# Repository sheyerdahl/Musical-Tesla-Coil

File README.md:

Welcome
======
A DRSSTC (Dual Resonant Solid State Tesla Coil) project that uses the ESP32-S3-WROOM-1 module as the microcontroller and wireless communication. 

My primary circuit uses the SKM100GB125DN IGBT

Notes
-------
The first revision (REV 1.0) being my first PCB, had quite a few issues and oversights. REV 2.0 will fix these issues, although it will be untested.
Some of the issues that were fixed:

Lack of OCD Comparator
Lack of peak detector circuit for measuring current
Lack of ZCD Comparator
USB-C footprint being incorrect
Slow diodes being used in the GDT circuit
Lack of mounting holes
Using built-in ADC of ESP32, an external one would have significantly more ENOB. (Effective Number Of Bits)
No Reverse polarity protection, no over current protection.

Credits
-------
Most design decisions were made because of Mads Barnkob and his awesome [website](https://kaizerpowerelectronics.dk/tesla-coils/drsstc-design-guide/) and [Youtube videos](https://www.youtube.com/@KaizerPowerElectronicsDk).

Thanks to those who worked on the [UD3 Board](https://github.com/Netzpfuscher/UD3), some of their hardware design was copied to this one.

[JAVATC3D](https://www.classictesla.com/java/javatc3d/javatc3d.html)

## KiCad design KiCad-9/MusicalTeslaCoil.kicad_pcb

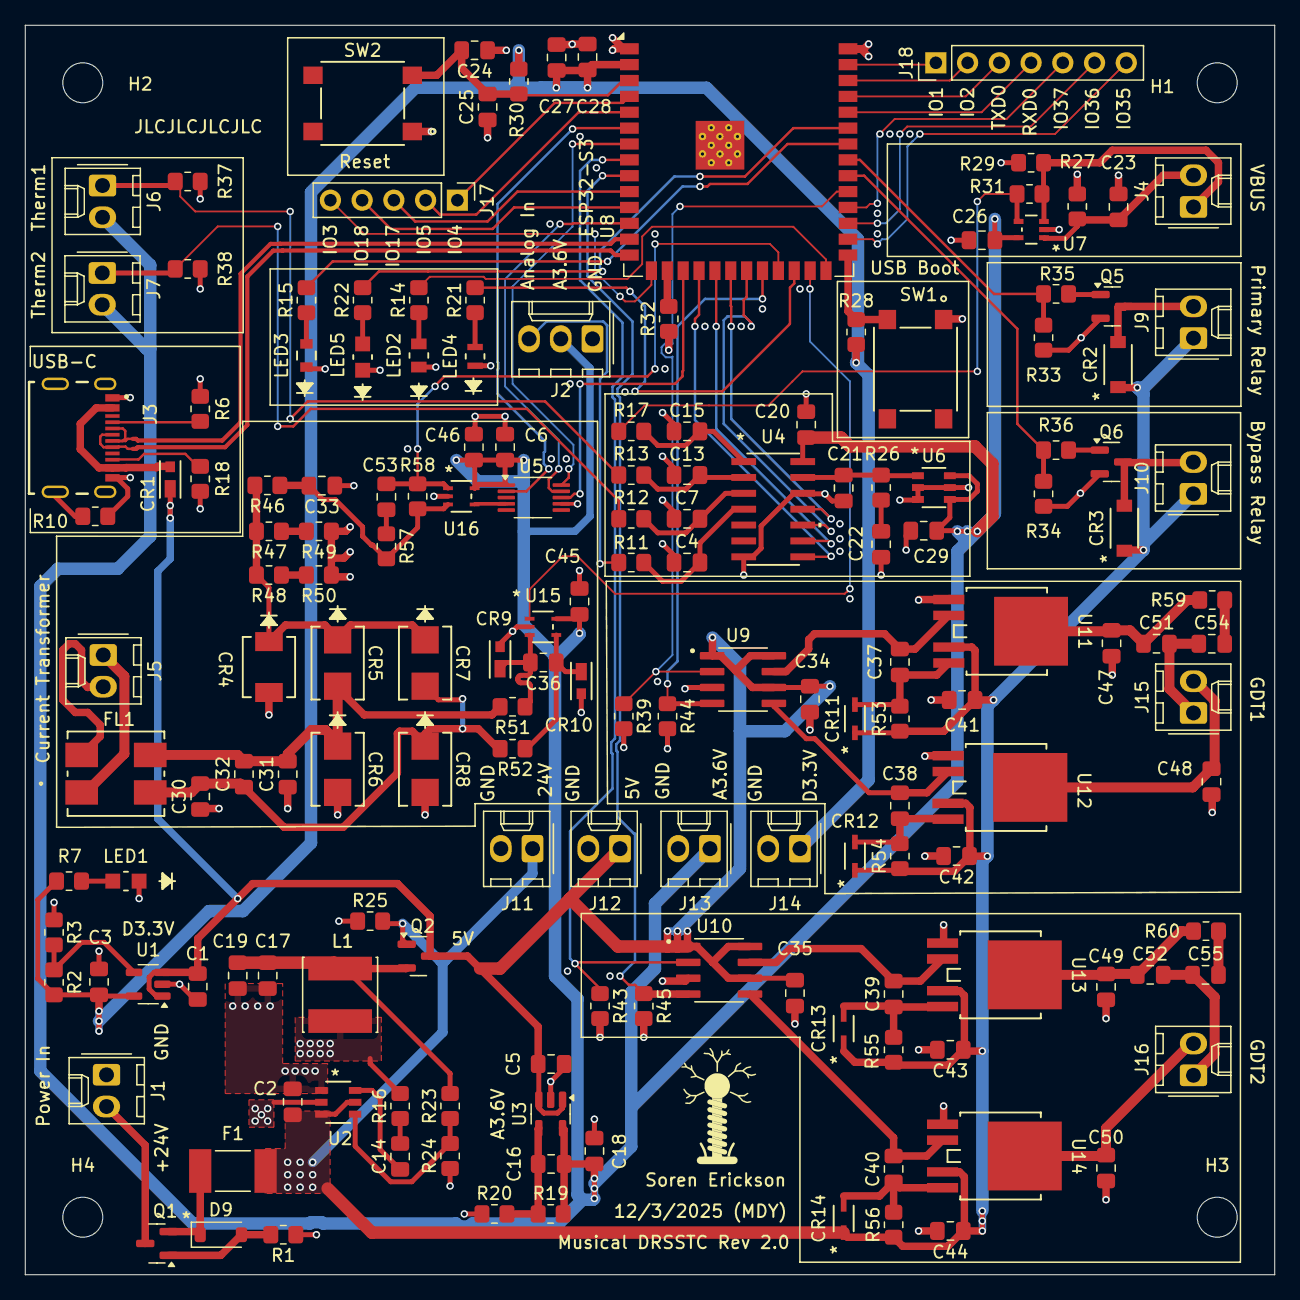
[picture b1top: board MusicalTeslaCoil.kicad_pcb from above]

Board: 4 copper layers, 100.0 x 100.0 mm, 169 parts (0 on the bottom side), 105 nets.

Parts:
C1, C3, C5, C18, C20, C22, C29, C51, C52: 2.2uF; C_0805_2012Metric_Pad1.18x1.45mm_HandSolder
C2, C17, C19, C27, C28: 10uF; C_0805_2012Metric_Pad1.18x1.45mm_HandSolder
C4, C7, C13, C15, C16, C23: 10nF; C_0805_2012Metric_Pad1.18x1.45mm_HandSolder
C6, C25, C45, C46, C54, C55: 1uF; C_0805_2012Metric_Pad1.18x1.45mm_HandSolder
C14, C24, C26, C37, C38, C39, C40: 0.1uF; C_0805_2012Metric_Pad1.18x1.45mm_HandSolder
C21, C32, C47, C48, C49, C50: 1nF; C_0805_2012Metric_Pad1.18x1.45mm_HandSolder
C30, C31, C33, C36: 150pF; C_0805_2012Metric_Pad1.18x1.45mm_HandSolder
C34, C35, C41, C42, C43, C44: 4.7uF; C_0805_2012Metric_Pad1.18x1.45mm_HandSolder
C53: 470pF; C_0805_2012Metric_Pad1.18x1.45mm_HandSolder
CR1, CR9, CR10: MSS1P4-M3/89A; DIODE_MSP3V3
CR2, CR3: 1N4007FL; CR_SOD-123FL_SME
CR4: SMBJ3V3-E3/52; CR_V3-E3&slash_52_VIS
CR5, CR6, CR7, CR8: ES2B-E3/52T; DO-214AA_VIS
CR11, CR12, CR13, CR14: 1N4148WS-7-F; CR_SOD323_MCC
D9: BZT52C15-7-F; D_SOD-123
F1: 0ZCG0050AF2C; FUSER_0ZCG0050AF2C
FL1: WCM 7060FASF-701-LM; FL4_WCM7060_TTA
H1, H2, H3, H4: MountingHole; MountingHole_3.2mm_M3
J1: Power in; Molex_KK-254_AE-6410-02A_1x02_P2.54mm_Vertical
J2: Conn_01x03; Molex_KK-254_AE-6410-03A_1x03_P2.54mm_Vertical
J3: USB4215-03-A; USB4215_03_A
J4: VBUS; Molex_KK-254_AE-6410-02A_1x02_P2.54mm_Vertical
J5: Current Transformer; Molex_KK-254_AE-6410-02A_1x02_P2.54mm_Vertical
J6: NTC Thermistor 1; Molex_KK-254_AE-6410-02A_1x02_P2.54mm_Vertical
J7: NTC Thermistor 2; Molex_KK-254_AE-6410-02A_1x02_P2.54mm_Vertical
J9: Primary Relay; Molex_KK-254_AE-6410-02A_1x02_P2.54mm_Vertical
J10: Soft Start Bypass Relay; Molex_KK-254_AE-6410-02A_1x02_P2.54mm_Vertical
J11, J12, J13, J14: Conn_01x02; Molex_KK-254_AE-6410-02A_1x02_P2.54mm_Vertical
J15: GDT1; Molex_KK-254_AE-6410-02A_1x02_P2.54mm_Vertical
J16: GDT2; Molex_KK-254_AE-6410-02A_1x02_P2.54mm_Vertical
J17: Conn_01x05; PinHeader_1x05_P2.54mm_Vertical
J18: Conn_01x07; PinHeader_1x07_P2.54mm_Vertical
L1: VLS6045EX-150M; VLS6045EX_150M
LED1, LED5: LTST-C170GKT; LED_LTST-C170GKT_LTO
LED2: LTST-C170KFKT; LED_LTST-C170KFKT_LTO
LED3: LTST-C171KRKT; LED_LTST-C171_LTO
LED4: LTST-C170KSKT; LED_LTST-C170KSKT_LTO
Q1: GSF3407; SOT-23
Q2: SSF7912; SOT-23
Q5, Q6: 2N7002K; SOT-23
R1, R6, R18: 5.1k; R_0805_2012Metric_Pad1.20x1.40mm_HandSolder
R2, R19, R24, R29, R31: 3k; R_0805_2012Metric_Pad1.20x1.40mm_HandSolder
R3: 15k; R_0805_2012Metric_Pad1.20x1.40mm_HandSolder
R7, R14, R15, R21, R22, R57: 150; R_0805_2012Metric_Pad1.20x1.40mm_HandSolder
R10: 100k; R_0805_2012Metric_Pad1.20x1.40mm_HandSolder
R11, R12, R13, R17, R37, R38, R46, R51, R52, R53, R54, R55, R56: 1k; R_0805_2012Metric_Pad1.20x1.40mm_HandSolder
R16: 0; R_0805_2012Metric_Pad1.20x1.40mm_HandSolder
R20: 16.5k; R_0805_2012Metric_Pad1.20x1.40mm_HandSolder
R23: 22k; R_0805_2012Metric_Pad1.20x1.40mm_HandSolder
R25, R28, R30, R32, R33, R34, R39, R43, R44, R45: 10k; R_0805_2012Metric_Pad1.20x1.40mm_HandSolder
R26, R35, R36: 51; R_0805_2012Metric_Pad1.20x1.40mm_HandSolder
R27: 1.5k; R_0805_2012Metric_Pad1.20x1.40mm_HandSolder
R47, R48, R49, R50: 3.3 0.5W; R_0805_2012Metric_Pad1.20x1.40mm_HandSolder
R58: 200k; R_0805_2012Metric_Pad1.20x1.40mm_HandSolder
R59, R60: 15; R_0805_2012Metric_Pad1.20x1.40mm_HandSolder
SW1: USB Boot; SO4_222A-M-V-B_CTS
SW2: Reset; SO4_222A-M-V-B_CTS
U1, U3: TLV75801PDBV; SOT-23-5
U2: TPP362082-T6TR; TSOT23-6-A_TPK
U4: MCP3204T-CI/SL; SOIC14-N_MC_MCH
U5: MCP48FVB11
U6: MCP1501T-33E/CHY; SOT-23-6_CHY_MCH
U7: MCP6006UT-E/LT; SC70-5_LT_MCH
U8: ESP32-S3-WROOM-1
U9, U10: UCC27423DR; SOIC127P599X175-8N
U11, U12, U13, U14: DMC4029SK4-13; TO252-4_DMC4029SK4-13_DIO
U15, U16: NCS2250SQ2T2G; SC70-5_2P2X1P35_ONS

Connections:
5V: C1.2, C5.2, C34.2, C35.2, CR1.1, J12.1, Q2.3 (D), U1.1 (IN), U1.3 (EN), U3.1 (IN), U3.3 (EN), U9.1 (ENBA), U9.6 (VDD), U9.8 (ENBB), U10.1 (ENBA), U10.6 (VDD), U10.8 (ENBB)
24V: C2.1, C41.1, C42.1, C43.1, C44.1, CR2.1, CR3.1, CR11.1, CR12.1, CR13.1, CR14.1, F1.1, J9.1, J10.1, J11.1, Q2.1 (G), R25.2, R53.1, R54.1, R55.1, R56.1, U2.3 (VIN), U2.5 (EN), U11.3 (P-Chan_S), U12.3 (P-Chan_S), U13.3 (P-Chan_S), U14.3 (P-Chan_S)
A3.6V: C6.2, C16.2, C18.2, C20.2, C26.2, C29.2, C45.2, C46.2, J2.2, J6.2, J7.2, J13.1, R19.2, U3.5 (OUT), U4.14 (VDD), U5.1 (VDD), U6.4 (*SHDN), U6.6 (VDD), U7.5 (V+), U15.5 (V+), U16.5 (V+)
ADC_CLK: U4.11 (CLK), U8.20 (IO12)
ADC_CS: U4.8 (*CS/SHDN), U8.18 (IO10)
ADC_DIN: U4.9 (DIN), U8.19 (IO11)
ADC_DOUT: U4.10 (DOUT), U8.21 (IO13)
BypassRelay: R34.1, R36.2, U8.32 (IO39)
CTOut: C33.2, R46.1, R57.2, R58.2, U16.3 (+)
D3.3V: C3.2, C27.2, C28.1, J14.1, R2.2, R7.2, R28.1, R30.1, U1.5 (OUT), U8.2 (3V3)
DACVOut: U5.4 (VOut), U16.4 (-)
DAC_CLK: U5.9 (SCK), U8.12 (IO8)
DAC_CS: U5.2 (*CS), U8.6 (IO6)
DAC_DIN: U5.10 (SDI), U8.7 (IO7)
DAC_DOUT: U5.8 (SDO), U8.17 (IO9)
GD1-A: R39.1, U8.31 (IO38), U9.2 (INA)
GD1-B: R44.1, U8.22 (IO14), U9.4 (INB)
GD2-A: R43.1, U8.8 (IO15), U10.2 (INA)
GD2-B: R45.1, U8.9 (IO16), U10.4 (INB)
GND: C1.1, C2.2, C3.1, C4.1, C5.1, C6.1, C7.1, C13.1, C15.1, C17.2, C18.1, C19.2, C20.1, C21.1, C22.1, C23.1, C24.1, C25.1, C26.1, C27.1, C28.2, C29.1, C30.1, C31.1, C33.1, C34.1, C35.1, C41.2, C42.2, C43.2, C44.2, C45.1, C46.1, C47.2, C48.2, C49.2, C50.2, CR4.2, CR6.2, CR8.2, CR9.2, CR10.2, J1.1, J2.1, J3.A1_B12 (GND_A), J3.B1_A12 (GND_B), J11.2, J12.2, J13.2, J14.2, LED1.1, LED2.1, LED3.1, LED4.1, LED5.1, Q5.2 (S), Q6.2 (S), R1.1, R3.1, R6.1, R10.2, R18.1, R20.1, R24.1, R25.1, R27.1, R29.1, R32.1, R33.2, R34.2, R37.2, R38.2, R39.2, R43.2, R44.2, R45.2, R49.1, R50.1, SW1.1 (A), SW2.1 (A), U1.2 (GND), U2.1 (GND), U3.2 (GND), U4.7 (DGND), U4.12 (AGND), U5.7 (GND), U6.2 (GND), U6.3 (GND), U6.5 (GND), U7.2 (V-), U8.1 (GND), U8.40 (GND), U8.41 (GND), U9.3 (GND), U10.3 (GND), U11.1 (N-Chan_S), U12.1 (N-Chan_S), U13.1 (N-Chan_S), U14.1 (N-Chan_S), U15.2 (V-), U16.2 (V-)
IO1: J18.1, U8.39 (IO1)
IO2: J18.2, U8.38 (IO2)
IO3: J17.5, U8.15 (IO3)
IO4: J17.1, U8.4 (IO4)
IO5: J17.2, U8.5 (IO5)
IO17: J17.3, U8.10 (IO17)
IO18: J17.4, U8.11 (IO18)
IO35: J18.7, U8.28 (IO35)
IO36: J18.6, U8.29 (IO36)
IO37: J18.5, U8.30 (IO37)
LED1: R15.2, U8.34 (IO41)
LED2: R22.2, U8.35 (IO42)
LED3: R14.2, U8.26 (IO45)
LED4: R21.2, U8.24 (IO47)
unnamed: C14.2, R16.1
unnamed: C22.2, R26.1
unnamed: C30.2, C32.1, CR7.2, CR8.1, FL1.3, R52.2
unnamed: C31.2, C32.2, CR5.2, CR6.1, FL1.4, R51.2
unnamed: C53.2, R57.1
unnamed: C54.2, R59.2
unnamed: C55.2, R60.2
unnamed: CR4.1, CR5.1, CR7.1, R46.2, R47.2, R48.2
unnamed: D9.2 (A), Q1.1 (G), R1.2
unnamed: D9.1 (K), F1.2, Q1.2 (S)
unnamed: J1.2, Q1.3 (D)
unnamed: J2.3, R11.2
unnamed: J3.A5 (CC1), R6.2
unnamed: J3.B5 (CC2), R18.2
unnamed: J3.SH4 (SHIELD__3), R10.1
unnamed: CR1.2, J3.A4_B9 (VBUS_A), J3.B4_A9 (VBUS_B)
unnamed: J4.1, R29.2, R31.2, U7.3 (-)
unnamed: C23.2, J4.2, R27.2, U7.1 (+)
unnamed: FL1.2, J5.1
unnamed: FL1.1, J5.2
unnamed: CR2.2, J9.2, Q5.3 (D)
unnamed: CR3.2, J10.2, Q6.3 (D)
unnamed: C51.1, C54.1, J15.1
unnamed: C48.1, J15.2, U12.5 (Drain)
unnamed: C52.1, C55.1, J16.1
unnamed: C50.1, J16.2, U14.5 (Drain)
unnamed: LED1.2, R7.1
unnamed: LED2.2, R14.1
unnamed: LED3.2, R15.1
unnamed: LED4.2, R21.1
unnamed: LED5.2, R22.1
unnamed: C17.1, C19.1, L1.2, Q2.2 (S), R23.2
unnamed: Q5.1 (G), R35.1
unnamed: Q6.1 (G), R36.1
unnamed: R47.1, R49.2
unnamed: R48.1, R50.2
unnamed: R28.2, SW1.2 (B), U8.27 (IO0)
unnamed: C24.2, C25.2, R30.2, SW2.2 (B), U8.3 (EN)
unnamed: R2.1, R3.2, U1.4 (FB)
unnamed: L1.1, R16.2, U2.2 (SW)
unnamed: C14.1, U2.6 (VBST)
unnamed: R23.1, R24.2, U2.4 (VFB)
unnamed: C16.1, R19.1, R20.2, U3.4 (FB)
unnamed: C15.2, R17.1, U4.1 (CH0)
unnamed: C13.2, R13.1, U4.2 (CH1)
unnamed: C7.2, R12.1, U4.3 (CH2)
unnamed: C4.2, R11.1, U4.4 (CH3)
unnamed: C21.2, R26.2, U4.13 (VREF), U6.1 (OUT)
unnamed: R32.2, U8.16 (IO46)
unnamed: C39.2, U10.7 (OUTA), U13.2 (N-Chan_G)
unnamed: C40.2, U10.5 (OUTB), U14.2 (N-Chan_G)
unnamed: C47.1, C51.2, R59.1, U11.5 (Drain)
unnamed: C37.2, U9.7 (OUTA), U11.2 (N-Chan_G)
unnamed: C37.1, CR11.2, R53.2, U11.4 (P-Chan_G)
unnamed: C38.2, U9.5 (OUTB), U12.2 (N-Chan_G)
unnamed: C38.1, CR12.2, R54.2, U12.4 (P-Chan_G)
unnamed: C49.1, C52.2, R60.1, U13.5 (Drain)
unnamed: C39.1, CR13.2, R55.2, U13.4 (P-Chan_G)
unnamed: C40.1, CR14.2, R56.2, U14.4 (P-Chan_G)
unnamed: C36.2, CR9.1, R51.1, U15.3 (+)
unnamed: C36.1, CR10.1, R52.1, U15.4 (-)
OCDInterrupt: C53.1, R58.1, U8.23 (IO21), U16.1
PrimaryRelay: R33.1, R35.2, U8.33 (IO40)
RXD0: J18.4, U8.36 (RXD0)
TXD0: J18.3, U8.37 (TXD0)
Therm1: J6.1, R13.2, R37.1
Therm2: J7.1, R12.2, R38.1
USB_D+: J3.A6 (DP1), J3.B6 (DP2), U8.14 (USB_D+)
USB_D-: J3.A7 (DN1), J3.B7 (DN2), U8.13 (USB_D-)
VBUS: R17.2, R31.1, U7.4
ZCDInterrupt: U8.25 (IO48), U15.1

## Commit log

2025-08-15 Renamed MusicalTeslaCoil folder to KiCad-9
2025-08-15 Create LICENSE
2025-10-17 Added web app
2025-10-28 Updated web app
2025-11-05 Added midi control
2025-11-07 Added midi octave slider
2025-11-07 Added ESP32 firmware
2025-11-07 Fixed crash on midi song ending
2025-11-07 Added build to .gitignore
2025-11-08 Added support for chords in midi playback
2025-11-12 Driver board can now reconnect BLE connection
2025-11-17 Added Chord Swap Time slider.
2025-11-17 Set max duty cycle to 10%
2025-12-04 Uploaded Rev 2.0
2025-12-04 Update README to clarify IGBT usage
2025-12-04 Added margin to sliders
